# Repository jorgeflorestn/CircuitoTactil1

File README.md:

# Circuito Tactil NTC UADY-CICY
Circuito para la detección de contacto en sensores nanoestructurados.

## Por hacer y revisar (de prioritario a no urgente)
- **Checar valores de _resistencias y capacitores_.**
<sub>(los del regulador deben ser 10uF en ambas salidas para evitar ruido, poner en paralelo uno de 100nf ceramico para reducir la Rint de ambos)</sub>
- Hacer tabla con características de mcu/mux/potdig/opamp para presentar a Francis y compararlo con equipo Keysight 34980A y 32923A
- ~~Añadir capacitores al lado de la entrada de 3.3v MCU ✓~~
- ~~Controlar la salida 2 del regulador para encender/apagar circuitos ✓~~ (checar consumo? aguanta el ic?)
- ~~Conectar MCU a pines ✓~~
- ~~Revisar mosfet Q1, se están usando como canal P y no N ✓~~
- ~~Validar secuencia en MUXes ✓~~(Checar que cable plano tenga los mismos pines en ambos extremos 1:1)
- ~~Editar footprint de nina para quitar todos los gpio no usados ✓~~
- ~~Validar conexión spi y componentes para micro SD ✓~~
- ~~Etiquetas en pines. ✓~~
- ~~tapar vias no importantes (reduciendo su tamaño <13 mils) ✓~~

## Extras a añadir
- ~~Añadir headers para sacar I2C y SPI ✓~~
- ~~Añadir testpoints en muxes ✓~~
- ~~Jumper para saltar de 3.3v a 5v ✓~~

### Si nos da tiempo 
- Añadir ic para carga y descarga de baterías (queda un espacio grande donde podemos añadir el cargador de pilas)
**(Si se añade, se debe aislar los 5v del usb y los 4.2 de la pila)**.
- Integrar ADC ADS1220 (FUTURO (puerto i2c disponible))
- ~~Añadir conector plano de +42 pines (básicamente se añadió en el punto de los testpoints en muxes)~~

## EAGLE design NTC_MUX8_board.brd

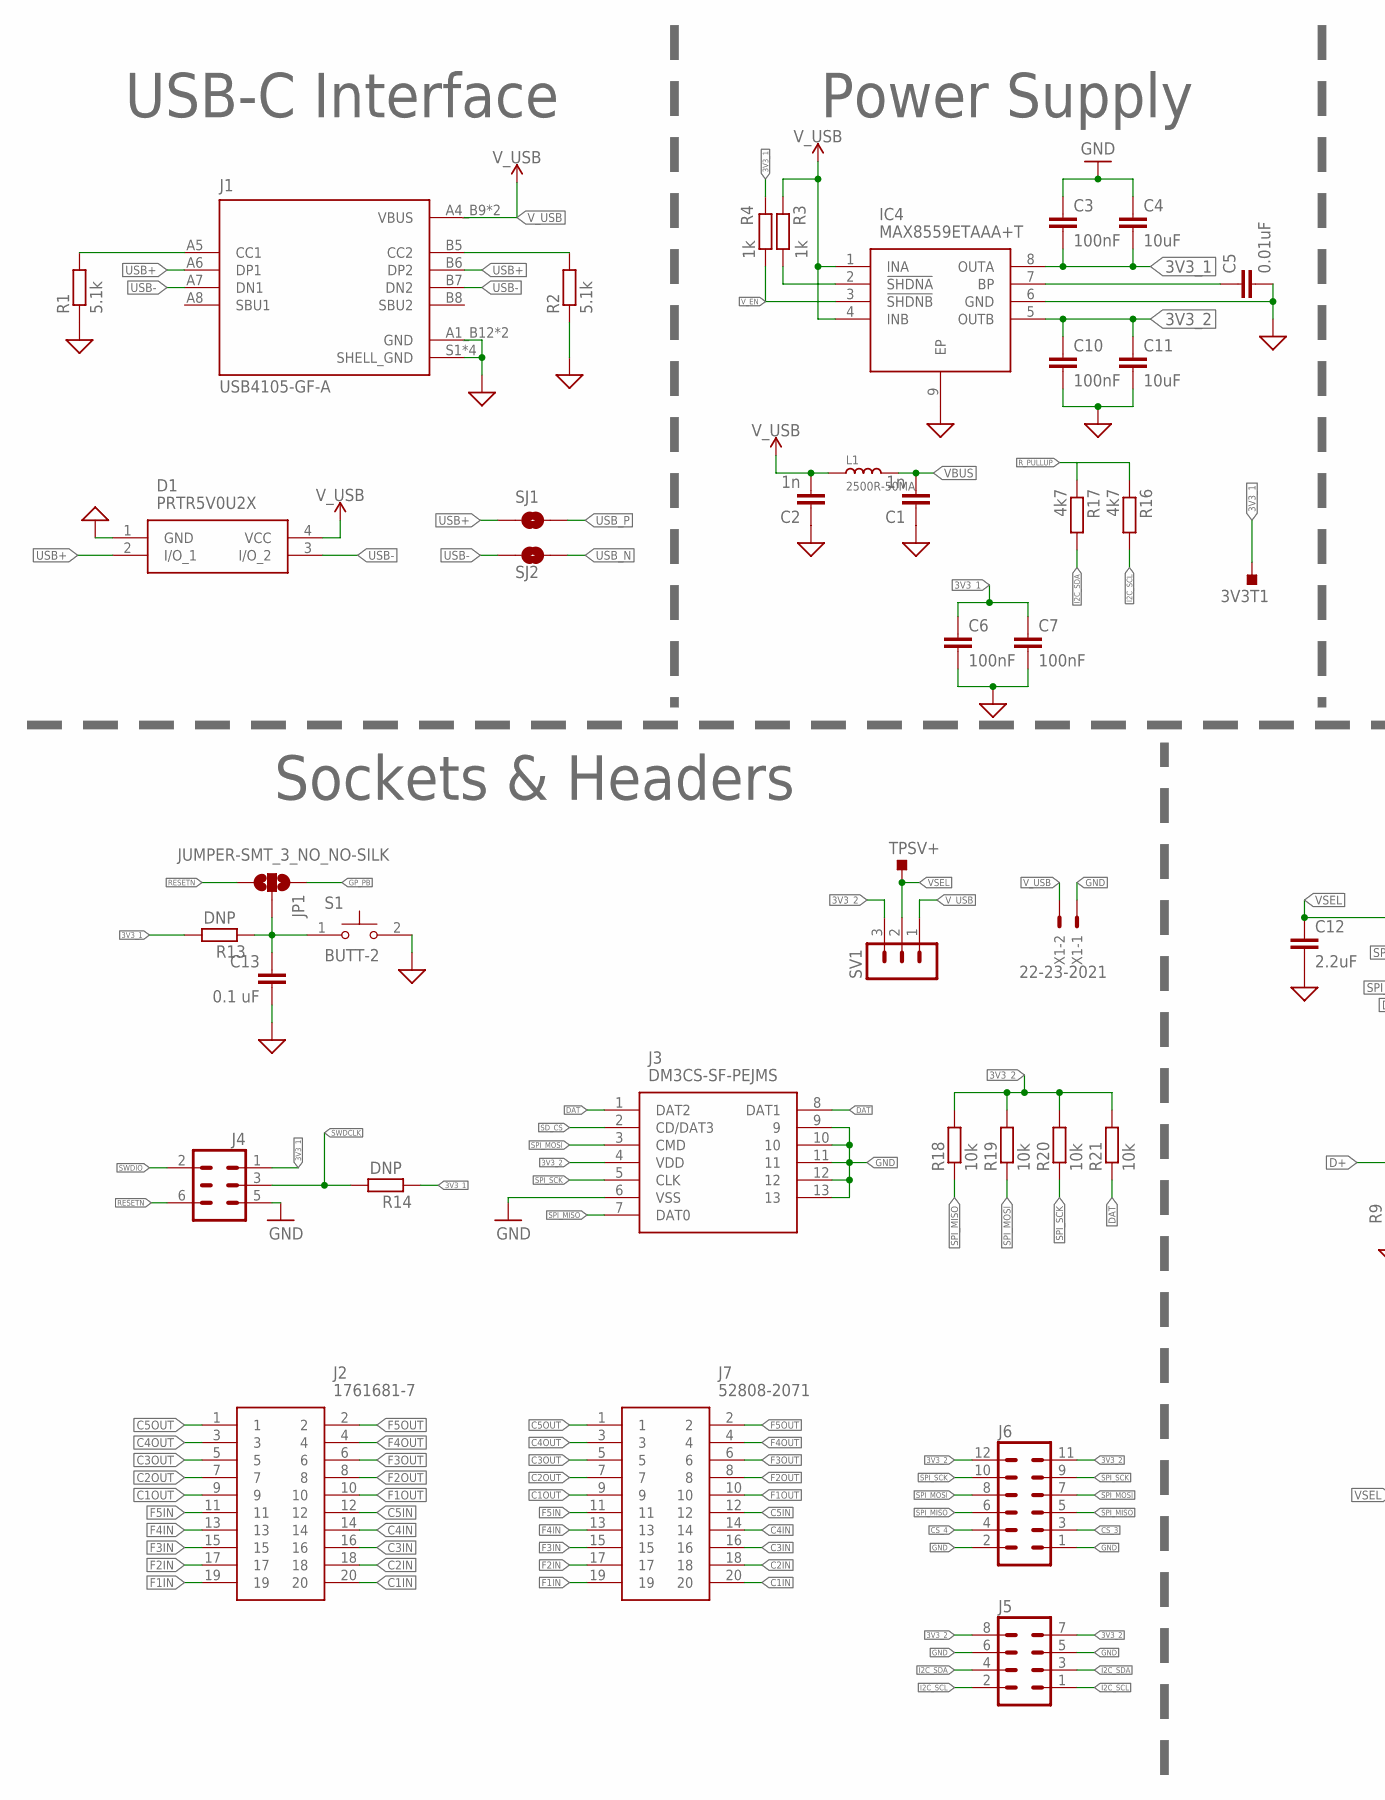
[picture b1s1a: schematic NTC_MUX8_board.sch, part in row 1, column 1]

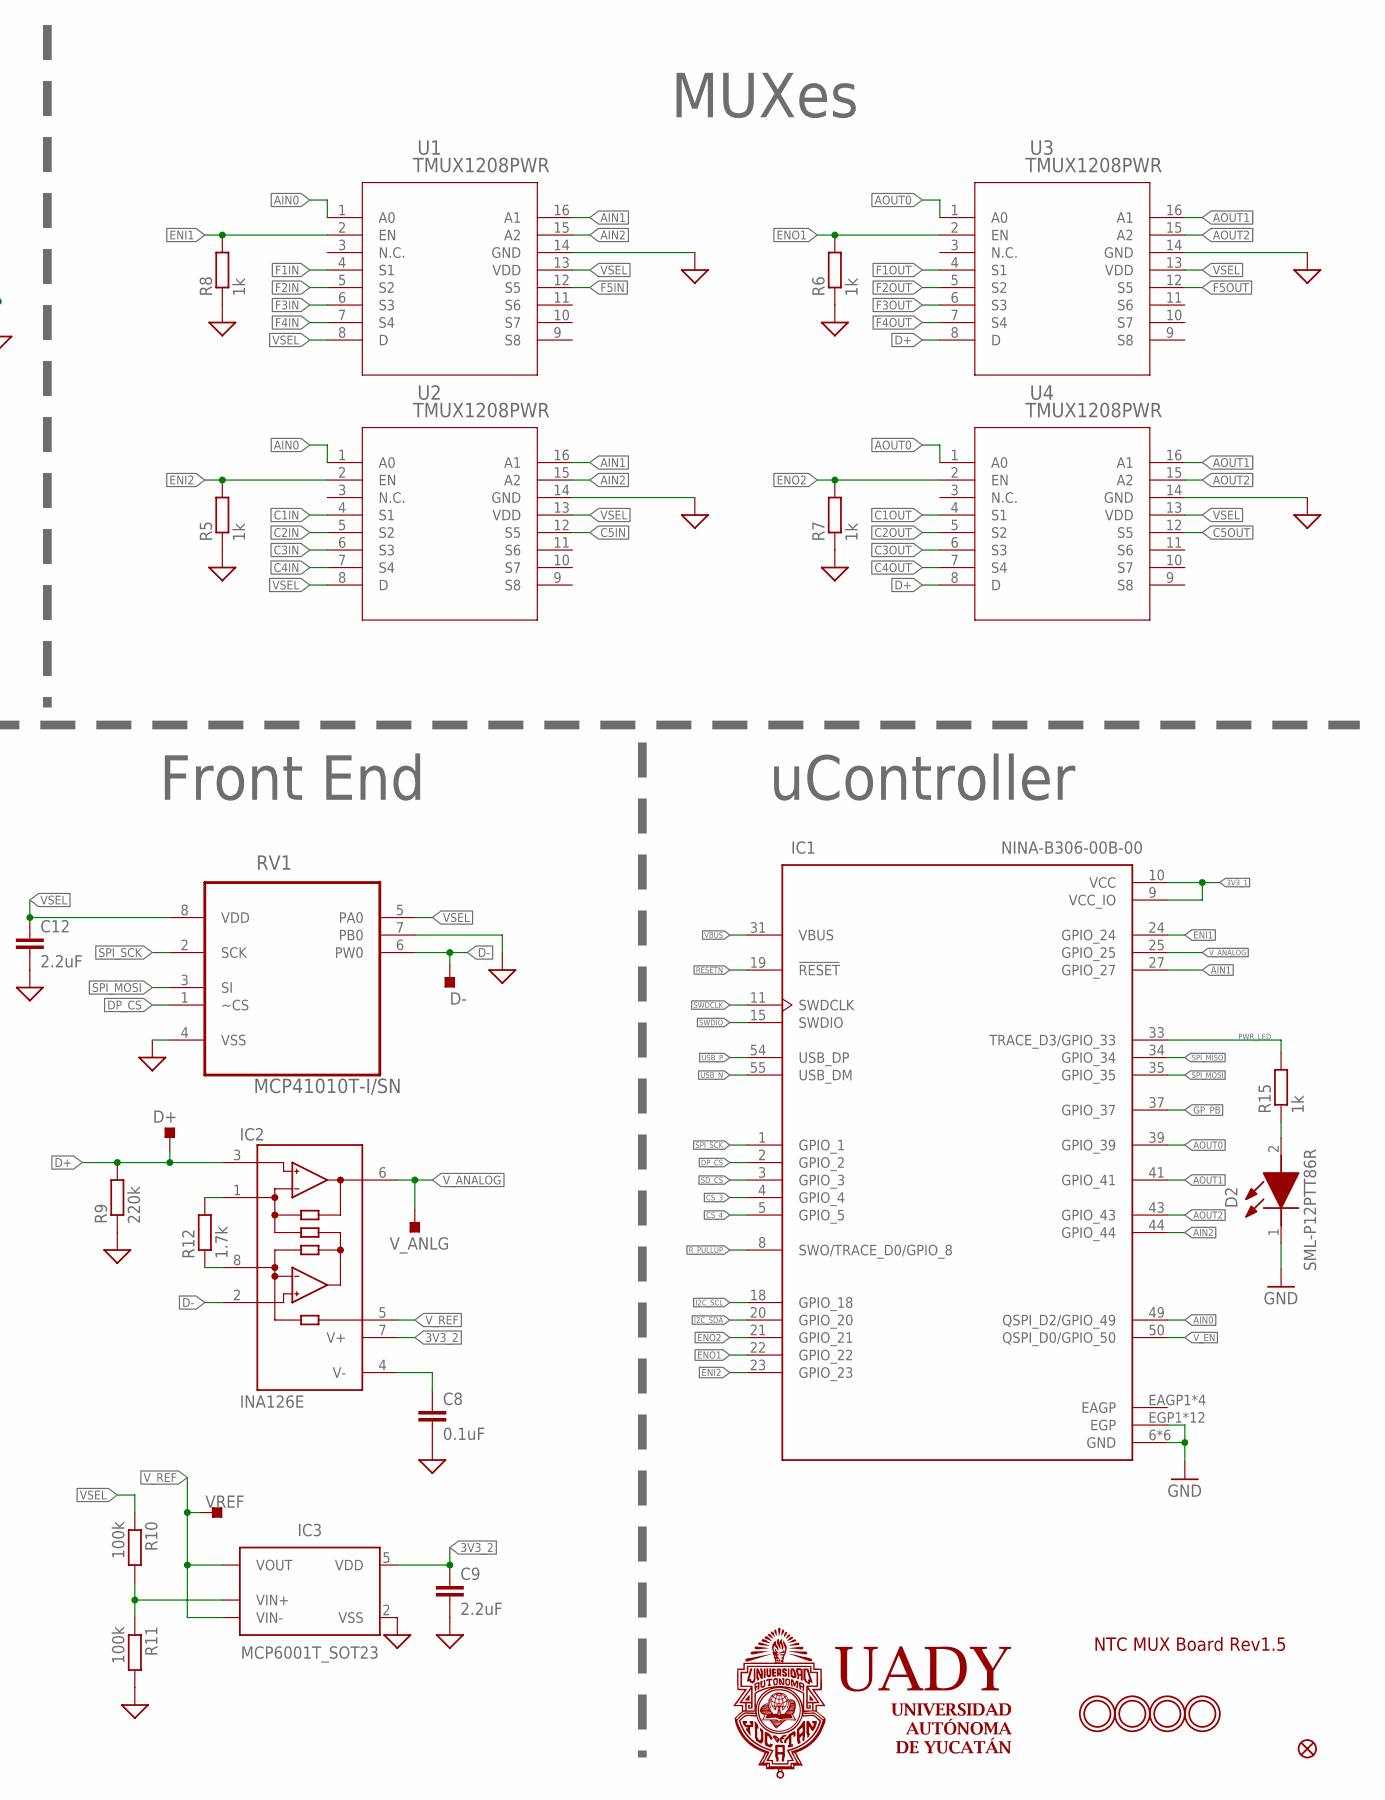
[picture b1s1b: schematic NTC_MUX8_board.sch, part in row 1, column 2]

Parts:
3V3T1: TESTPOINT_TPS-SMD-10SN; TESTPOINT_SMD-10SN
C1, C2: 1n; C0603
C3, C6, C7, C10: 100nF; C0603
C4, C11: 10uF; C0603
C5: 0.01uF; C0603
C8: 0.1uF; C0603
C9, C12: 2.2uF; C0603
C13: 0.1 uF; C0603
D1: PRTR5V0U2X
D2: SML-P12PTT86R; LEDC1006X25N
D+: TESTPOINT_TPS-SMD-10SN; TESTPOINT_SMD-10SN
D-: TESTPOINT_TPS-SMD-10SN; TESTPOINT_SMD-10SN
FID1: FIDUCIAL_1MM
IC1: NINA-B306-00B-00; XCVR_NINA-B306-00B-00
IC2: INA126E; MSOP08
IC3: MCP6001T_SOT23; SOT95P280X145-5N
IC4: MAX8559ETAAA+T; SON65P300X300X80-9N
J1: USB4105-GF-A; GCT_USB4105-GF-A
J2: 1761681-7; SHDR20W66P254_2X10_3302X883X92
J3: DM3CS-SF-PEJMS; DM3CSSFPEJMS
J4: DNP; 2X03-TP1
J5: MA04-2
J6: MA06-2
J7: 52808-2071; 528082071
JP1: JUMPER-SMT_3_NO_NO-SILK; SMT-JUMPER_3_NO_NO-SILK
L1: 2500R-50MA; L0603
R1, R2: 5.1k; R0603
R3, R4, R5, R6, R7, R8, R15: 1k; R0603
R9: 220k; R0603
R10, R11: 100k; R0603
R12: 1.7k; R0603
R13, R14: DNP; R0603
R16, R17: 4k7; R0603
R18, R19, R20, R21: 10k; R0603
RV1: MCP41010T-I/SN; SOIC127P600X175-8N
S1: BUTT-2; SW_BUTT-2
SJ1, SJ2: JUMPER-SMT_2_NO_NO-SILK; SMT-JUMPER_2_NO_NO-SILK
SV1: MA03-1
TPSV+: TESTPOINT_TPS-SMD-10SN; TESTPOINT_SMD-10SN
U1, U2, U3, U4: TMUX1208PWR; PW_16_TEX
U$2, U$3, U$4, U$24: MOUNTINGHOLE2.5; MOUNTINGHOLE_2.5_PLATED
VREF: TESTPOINT_TPS-SMD-10SN; TESTPOINT_SMD-10SN
V_ANLG: TESTPOINT_TPS-SMD-10SN; TESTPOINT_SMD-10SN
X1: 22-23-2021

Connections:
3V3_1: 3V3T1.TP, C3.2, C4.2, C6.1, C7.1, IC1.9 (VCC_IO), IC1.10 (VCC), IC4.8 (OUTA), J4.1, R4.1, R13.2, R14.1
3V3_2: C9.1, C10.1, C11.1, IC2.7 (V+), IC3.5 (VDD), IC4.5 (OUTB), J3.4 (VDD), J5.7, J5.8, J6.11, J6.12, R18.2, R19.2, R20.2, R21.2, SV1.3
AIN0: IC1.49 (QSPI_D2/GPIO_49), U1.1 (A0), U2.1 (A0)
AIN1: IC1.27 (GPIO_27), U1.16 (A1), U2.16 (A1)
AIN2: IC1.44 (GPIO_44), U1.15 (A2), U2.15 (A2)
AOUT0: IC1.39 (GPIO_39), U3.1 (A0), U4.1 (A0)
AOUT1: IC1.41 (GPIO_41), U3.16 (A1), U4.16 (A1)
AOUT2: IC1.43 (GPIO_43), U3.15 (A2), U4.15 (A2)
C1IN: J2.20, J7.20, U2.4 (S1)
C1OUT: J2.9, J7.9, U4.4 (S1)
C2IN: J2.18, J7.18, U2.5 (S2)
C2OUT: J2.7, J7.7, U4.5 (S2)
C3IN: J2.16, J7.16, U2.6 (S3)
C3OUT: J2.5, J7.5, U4.6 (S3)
C4IN: J2.14, J7.14, U2.7 (S4)
C4OUT: J2.3, J7.3, U4.7 (S4)
C5IN: J2.12, J7.12, U2.12 (S5)
C5OUT: J2.1, J7.1, U4.12 (S5)
CS_3: IC1.4 (GPIO_4), J6.3
CS_4: IC1.5 (GPIO_5), J6.4
D+: D+.TP, IC2.3 (+IN), R9.2, U3.8 (D), U4.8 (D)
D-: D-.TP, IC2.2 (-IN), RV1.6 (PW0)
DAT: J3.1 (DAT2), J3.8 (DAT1), R21.1
DP_CS: IC1.2 (GPIO_2), RV1.1 (~CS)
EAGP: IC1.EAGP1 (EAGP), IC1.EAGP2 (EAGP), IC1.EAGP3 (EAGP), IC1.EAGP4 (EAGP)
ENI1: IC1.24 (GPIO_24), R8.2, U1.2 (EN)
ENI2: IC1.23 (GPIO_23), R5.2, U2.2 (EN)
ENO1: IC1.22 (GPIO_22), R6.2, U3.2 (EN)
ENO2: IC1.21 (GPIO_21), R7.2, U4.2 (EN)
F1IN: J2.19, J7.19, U1.4 (S1)
F1OUT: J2.10, J7.10, U3.4 (S1)
F2IN: J2.17, J7.17, U1.5 (S2)
F2OUT: J2.8, J7.8, U3.5 (S2)
F3IN: J2.15, J7.15, U1.6 (S3)
F3OUT: J2.6, J7.6, U3.6 (S3)
F4IN: J2.13, J7.13, U1.7 (S4)
F4OUT: J2.4, J7.4, U3.7 (S4)
F5IN: J2.11, J7.11, U1.12 (S5)
F5OUT: J2.2, J7.2, U3.12 (S5)
GND: C1.1, C2.1, C3.1, C4.1, C5.2, C6.2, C7.2, C8.2, C9.2, C10.2, C11.2, C12.2, C13.2, D1.1 (GND), D2.1 (K), IC1.6 (GND), IC1.12 (GND), IC1.14 (GND), IC1.26 (GND), IC1.30 (GND), IC1.53 (GND), IC1.EGP1 (EGP), IC1.EGP2 (EGP), IC1.EGP3 (EGP), IC1.EGP4 (EGP), IC1.EGP5 (EGP), IC1.EGP6 (EGP), IC1.EGP7 (EGP), IC1.EGP8 (EGP), IC1.EGP9 (EGP), IC1.EGP10 (EGP), IC1.EGP11 (EGP), IC1.EGP12 (EGP), IC3.2 (VSS), IC4.6 (GND), IC4.9 (EP), J1.A1_B12 (GND), J1.B1_A12 (GND), J1.S1 (SHELL_GND), J1.S2 (SHELL_GND), J1.S3 (SHELL_GND), J1.S4 (SHELL_GND), J3.6 (VSS), J3.9, J3.10, J3.11, J3.12, J3.13, J4.5, J5.5, J5.6, J6.1, J6.2, R1.1, R2.1, R5.1, R6.1, R7.1, R8.1, R9.1, R11.2, RV1.4 (VSS), RV1.7 (PB0), S1.2, U1.14 (GND), U2.14 (GND), U3.14 (GND), U4.14 (GND), X1.1
GP_PB: IC1.37 (GPIO_37), JP1.3
I2C_SCL: IC1.18 (GPIO_18), J5.1, J5.2, R16.2
I2C_SDA: IC1.20 (GPIO_20), J5.3, J5.4, R17.2
unnamed: J1.A5 (CC1), R1.2
unnamed: IC4.2 (!SHDNA), R3.2
unnamed: D2.2 (A), R15.1
unnamed: IC2.1 (RG), R12.2
unnamed: C5.1, IC4.7 (BP)
unnamed: IC2.8 (RG), R12.1
unnamed: C8.1, IC2.4 (V-)
unnamed: J1.B5 (CC2), R2.2
unnamed: IC3.3 (VIN+), R10.2, R11.1
PWR_LED: IC1.33 (TRACE_D3/GPIO_33), R15.2
RESET: C13.1, JP1.2, R13.1, S1.1
RESETN: IC1.19 (!RESET), J4.6, JP1.1
R_PULLUP: IC1.8 (SWO/TRACE_D0/GPIO_8), R16.1, R17.1
SD_CS: IC1.3 (GPIO_3), J3.2 (CD/DAT3)
SPI_MISO: IC1.34 (GPIO_34), J3.7 (DAT0), J6.5, J6.6, R18.1
SPI_MOSI: IC1.35 (GPIO_35), J3.3 (CMD), J6.7, J6.8, R19.1, RV1.3 (SI)
SPI_SCK: IC1.1 (GPIO_1), J3.5 (CLK), J6.9, J6.10, R20.1, RV1.2 (SCK)
SWDCLK: IC1.11 (SWDCLK), J4.3, R14.2
SWDIO: IC1.15 (SWDIO), J4.2
USB+: D1.2 (I/O_1), J1.A6 (DP1), J1.B6 (DP2), SJ1.1
USB-: D1.3 (I/O_2), J1.A7 (DN1), J1.B7 (DN2), SJ2.1
USB_N: IC1.55 (USB_DM), SJ2.2
USB_P: IC1.54 (USB_DP), SJ1.2
VBUS: C1.2, IC1.31 (VBUS), L1.2
VSEL: C12.1, R10.1, RV1.5 (PA0), RV1.8 (VDD), SV1.2, TPSV+.TP, U1.8 (D), U1.13 (VDD), U2.8 (D), U2.13 (VDD), U3.13 (VDD), U4.13 (VDD)
V_ANALOG: IC1.25 (GPIO_25), IC2.6 (OUT), V_ANLG.TP
V_EN: IC1.50 (QSPI_D0/GPIO_50), IC4.3 (!SHDNB), R4.2
V_REF: IC2.5 (REF), IC3.1 (VOUT), IC3.4 (VIN-), VREF.TP
V_USB: C2.2, D1.4 (VCC), IC4.1 (INA), IC4.4 (INB), J1.A4_B9 (VBUS), J1.B4_A9 (VBUS), L1.1, R3.1, SV1.1, X1.2

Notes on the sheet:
uController
Sockets & Headers
MUXes
Power Supply
USB-C Interface
Front End
NTC MUX Board Rev1.5

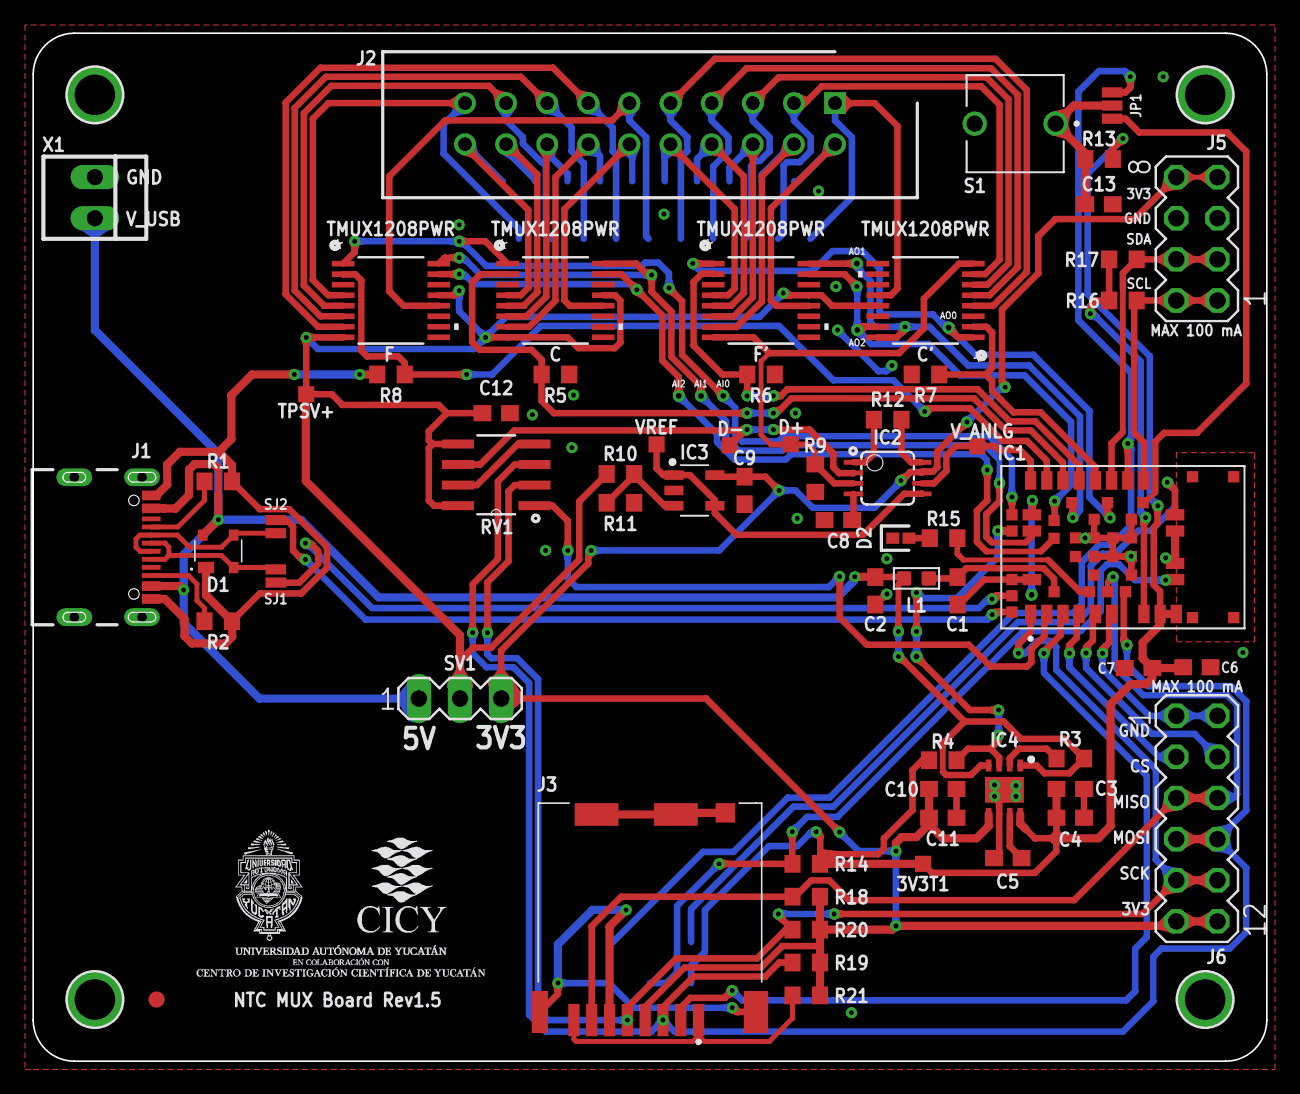
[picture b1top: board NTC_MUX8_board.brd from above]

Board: 2 copper layers, 76.2 x 63.5 mm, 71 parts (1 on the bottom side), 72 nets.

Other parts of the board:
U$5: UADY-CICY-MID

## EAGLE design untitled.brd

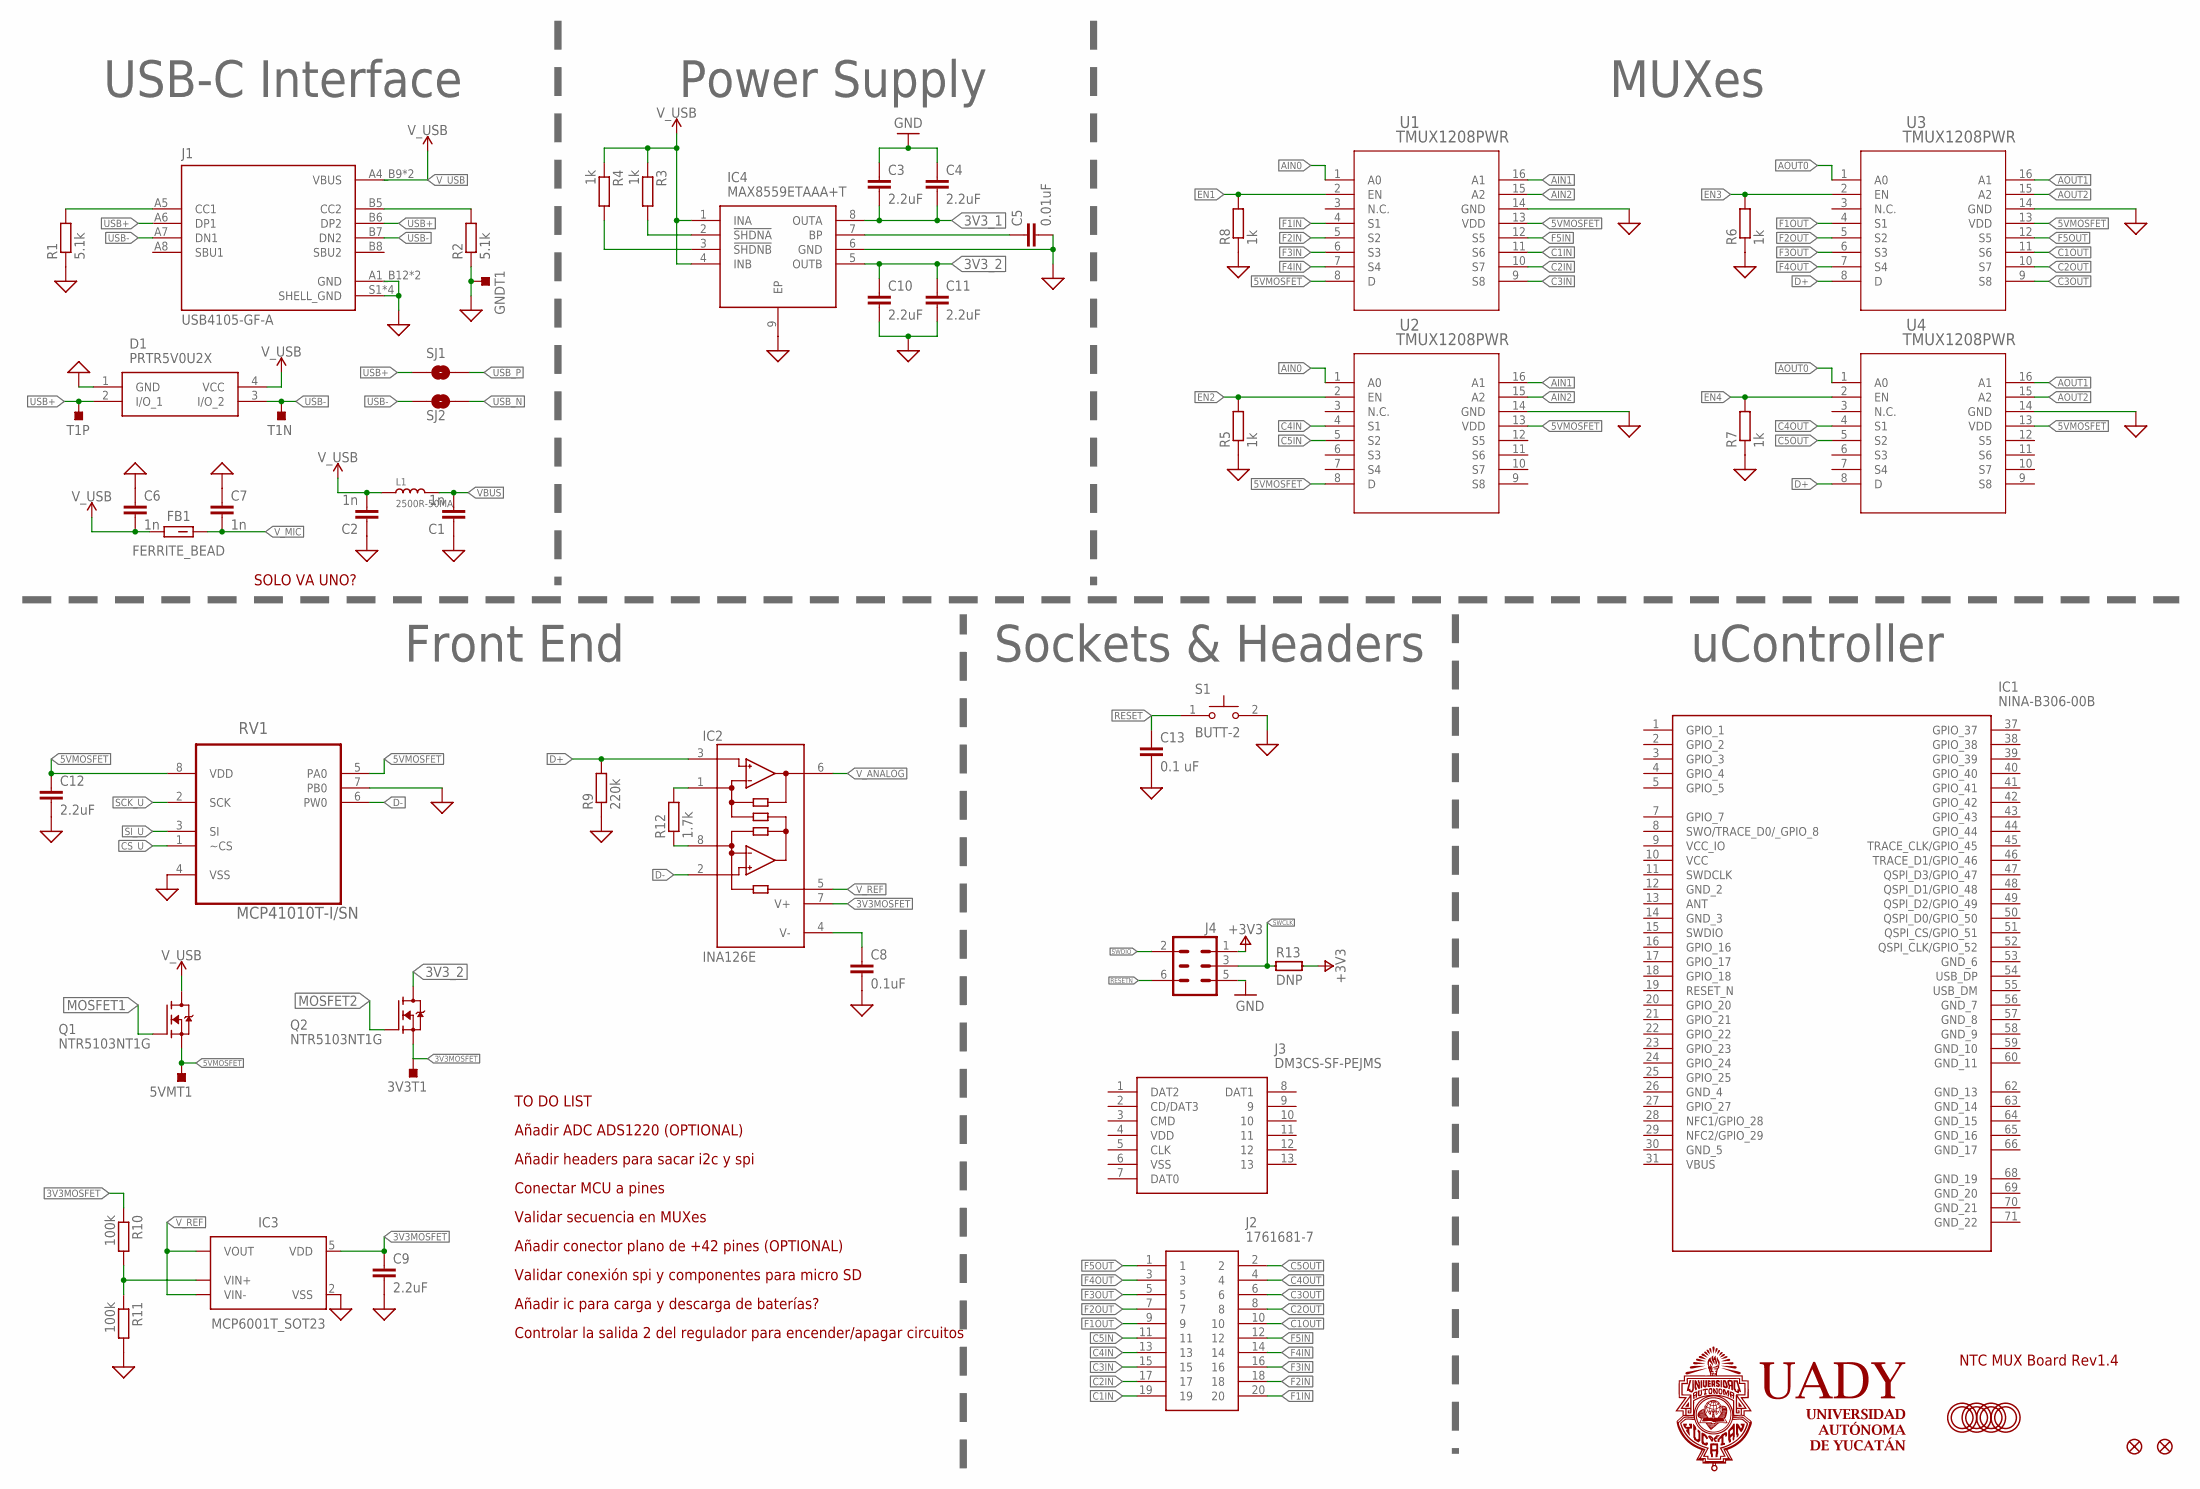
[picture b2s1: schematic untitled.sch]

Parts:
3V3T1, 5VMT1: TESTPOINT_TPS-SMD-10SN; TESTPOINT_SMD-10SN
C1, C2, C6, C7: 1n; C0603
C3, C4, C9, C10, C11, C12: 2.2uF; C0603
C5: 0.01uF; C0603
C8: 0.1uF; C0603
C13: 0.1 uF; C0603
D1: PRTR5V0U2X
FB1: FERRITE_BEAD; BEADC1608X95N
FID1, FID4: FIDUCIAL_1MM
GNDT1: TESTPOINT_TPS-SMD-10SN; TESTPOINT_SMD-10SN
IC1: NINA-B306-00B; NINAB30600B
IC2: INA126E; MSOP08
IC3: MCP6001T_SOT23; SOT95P280X145-5N
IC4: MAX8559ETAAA+T; SON65P300X300X80-9N
J1: USB4105-GF-A; GCT_USB4105-GF-A
J2: 1761681-7; SHDR20W66P254_2X10_3302X883X92
J3: DM3CS-SF-PEJMS; DM3CSSFPEJMS
J4: DNP; 2X03-TP1
L1: 2500R-50MA; L0603
Q1, Q2: NTR5103NT1G; SOT95P237X111-3N
R1, R2: 5.1k; R0603
R3, R4, R5, R6, R7, R8: 1k; R0603
R9: 220k; R0603
R10, R11: 100k; R0603
R12: 1.7k; R0603
R13: DNP; 0402-1005X55N
RV1: MCP41010T-I/SN; SOIC127P600X175-8N
S1: BUTT-2; SW_BUTT-2
SJ1, SJ2: JUMPER-SMT_2_NO_NO-SILK; SMT-JUMPER_2_NO_NO-SILK
T1N, T1P: TESTPOINT_TPS-SMD-10SN; TESTPOINT_SMD-10SN
U1, U2, U3, U4: TMUX1208PWR; PW_16_TEX
U$2, U$3, U$4, U$24: MOUNTINGHOLE2.5; MOUNTINGHOLE_2.5_PLATED

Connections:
3V3MOSFET: 3V3T1.TP, C9.1, IC2.7 (V+), IC3.5 (VDD), Q2.2 (S), R10.1
3V3_1: C3.2, C4.2, IC4.8 (OUTA)
3V3_2: C10.1, C11.1, IC4.5 (OUTB), Q2.3 (D)
5VMOSFET: 5VMT1.TP, C12.1, Q1.2 (S), RV1.5 (PA0), RV1.8 (VDD), U1.8 (D), U1.13 (VDD), U2.8 (D), U2.13 (VDD), U3.13 (VDD), U4.13 (VDD)
+3V3: J4.1, R13.1
AIN0: U1.1 (A0), U2.1 (A0)
AIN1: U1.16 (A1), U2.16 (A1)
AIN2: U1.15 (A2), U2.15 (A2)
AOUT0: U3.1 (A0), U4.1 (A0)
AOUT1: U3.16 (A1), U4.16 (A1)
AOUT2: U3.15 (A2), U4.15 (A2)
C1IN: J2.19, U1.11 (S6)
C1OUT: J2.10, U3.11 (S6)
C2IN: J2.17, U1.10 (S7)
C2OUT: J2.8, U3.10 (S7)
C3IN: J2.15, U1.9 (S8)
C3OUT: J2.6, U3.9 (S8)
C4IN: J2.13, U2.4 (S1)
C4OUT: J2.4, U4.4 (S1)
C5IN: J2.11, U2.5 (S2)
C5OUT: J2.2, U4.5 (S2)
CS_U: RV1.1 (~CS)
D+: IC2.3 (+IN), R9.2, U3.8 (D), U4.8 (D)
D-: IC2.2 (-IN), RV1.6 (PW0)
EN1: R8.2, U1.2 (EN)
EN2: R5.2, U2.2 (EN)
EN3: R6.2, U3.2 (EN)
EN4: R7.2, U4.2 (EN)
F1IN: J2.20, U1.4 (S1)
F1OUT: J2.9, U3.4 (S1)
F2IN: J2.18, U1.5 (S2)
F2OUT: J2.7, U3.5 (S2)
F3IN: J2.16, U1.6 (S3)
F3OUT: J2.5, U3.6 (S3)
F4IN: J2.14, U1.7 (S4)
F4OUT: J2.3, U3.7 (S4)
F5IN: J2.12, U1.12 (S5)
F5OUT: J2.1, U3.12 (S5)
GND: C1.1, C2.1, C3.1, C4.1, C5.2, C6.1, C7.1, C8.2, C9.2, C10.2, C11.2, C12.2, C13.2, D1.1 (GND), GNDT1.TP, IC3.2 (VSS), IC4.6 (GND), IC4.9 (EP), J1.A1_B12 (GND), J1.B1_A12 (GND), J1.S1 (SHELL_GND), J1.S2 (SHELL_GND), J1.S3 (SHELL_GND), J1.S4 (SHELL_GND), J4.5, R1.1, R2.1, R5.1, R6.1, R7.1, R8.1, R9.1, R11.2, RV1.4 (VSS), RV1.7 (PB0), S1.2, U1.14 (GND), U2.14 (GND), U3.14 (GND), U4.14 (GND)
MOSFET1: Q1.1 (G)
MOSFET2: Q2.1 (G)
unnamed: J1.A5 (CC1), R1.2
unnamed: IC4.2 (!SHDNA), R3.2
unnamed: IC4.3 (!SHDNB), R4.2
unnamed: IC2.1 (RG), R12.2
unnamed: C5.1, IC4.7 (BP)
unnamed: IC2.8 (RG), R12.1
unnamed: C8.1, IC2.4 (V-)
unnamed: J1.B5 (CC2), R2.2
unnamed: IC3.3 (VIN+), R10.2, R11.1
RESET: C13.1, S1.1
RESETN: J4.6
SCK_U: RV1.2 (SCK)
SI_U: RV1.3 (SI)
SWCLK: J4.3, R13.2
SWDIO: J4.2
USB+: D1.2 (I/O_1), J1.A6 (DP1), J1.B6 (DP2), SJ1.1, T1P.TP
USB-: D1.3 (I/O_2), J1.A7 (DN1), J1.B7 (DN2), SJ2.1, T1N.TP
USB_N: SJ2.2
USB_P: SJ1.2
VBUS: C1.2, L1.2
V_ANALOG: IC2.6 (OUT)
V_MIC: C7.2, FB1.2
V_REF: IC2.5 (REF), IC3.1 (VOUT), IC3.4 (VIN-)
V_USB: C2.2, C6.2, D1.4 (VCC), FB1.1, IC4.1 (INA), IC4.4 (INB), J1.A4_B9 (VBUS), J1.B4_A9 (VBUS), L1.1, Q1.3 (D), R3.1, R4.1

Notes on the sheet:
uController
Sockets & Headers
MUXes
Power Supply
USB-C Interface
Front End
NTC MUX Board Rev1.4
Añadir ADC ADS1220 (OPTIONAL)
Añadir headers para sacar i2c y spi
Conectar MCU a pines
Validar secuencia en MUXes
Añadir conector plano de +42 pines (OPTIONAL)
TO DO LIST
SOLO VA UNO?
Validar conexión spi y componentes para micro SD
Añadir ic para carga y descarga de baterías?
Controlar la salida 2 del regulador para encender/apagar circuitos

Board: 2 copper layers, 59 parts (0 on the bottom side), 55 nets, no tracks yet.

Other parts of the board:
U$5: UADY-CICY-MID

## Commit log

2023-02-10 Add files via upload
    1
2023-02-14 Reset arrange insert
2023-02-17 first edit
2023-02-17 usb c done
2023-02-17 lista actualizada de pendientes
    faltan algunas cosas, pero la base ya está para solo unir y rutear
2023-02-17 3d models updated
2023-02-24 detalles
    faltan los detalles marcados en el esquemático
2023-02-24 3d file
    falta rutear
2023-02-27 Pequeños errores y adición de mejoras
2023-02-27 renders pre-finales
2023-02-28 casi listo
    añadidas etiquetas y mejora del ruteo de algunas pistas
2023-02-28 añadidos los datasheets
2023-02-28 beta finalizada
    circuito listo a mi parecer
2023-02-28 primer gerber
    gerber y cotización
2023-02-28 minor corrections
    corrección v en seguidor
    y pistas
2023-03-01 test points on front end
2023-03-07 teardrops en vias y pines

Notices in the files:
parts and their libraries:
SparkFun-Jumpers: Licensing: Creative Commons ShareAlike 4.0 International - https://creativecommons.org/licenses/by-sa/4.0
Arduino-connectors: Copyright (c) 2016-2017 Arduino LLC.  All right reserved.
COPYRIGHT: Copyright (C) 2022 Ultra Librarian. All rights reserved.
